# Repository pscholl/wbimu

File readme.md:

A re-configurable standalone board including the latest Bosch inertial sensors. Includes a gyroscope, accelerometer, magnetometer, humidity, pressure and temperature. The board is 13x22mm large.

 The board can either be used battery-powered in a standalone fashion, or connected to a Linux machine via USB Type C.
 By using the Bosch BMF a fully reprogrammable ARM M0 core is included on the board, which can control the system in standalone operation. 
 The MCP2210 USB-SPI bridge can control all components when connected to a PC.
 Wireless communication is provided by Decawave's DWM100 modules, which provides ultra-wideband communication and ranging with an accuracy of 10cms.
 Power can either be supplied via USB or by a li-ion battery, a charger is included on the board.

 The system is currently under testing, ieee802.15.4- and tcp/ip-compliant linux drivers are currently being developed.

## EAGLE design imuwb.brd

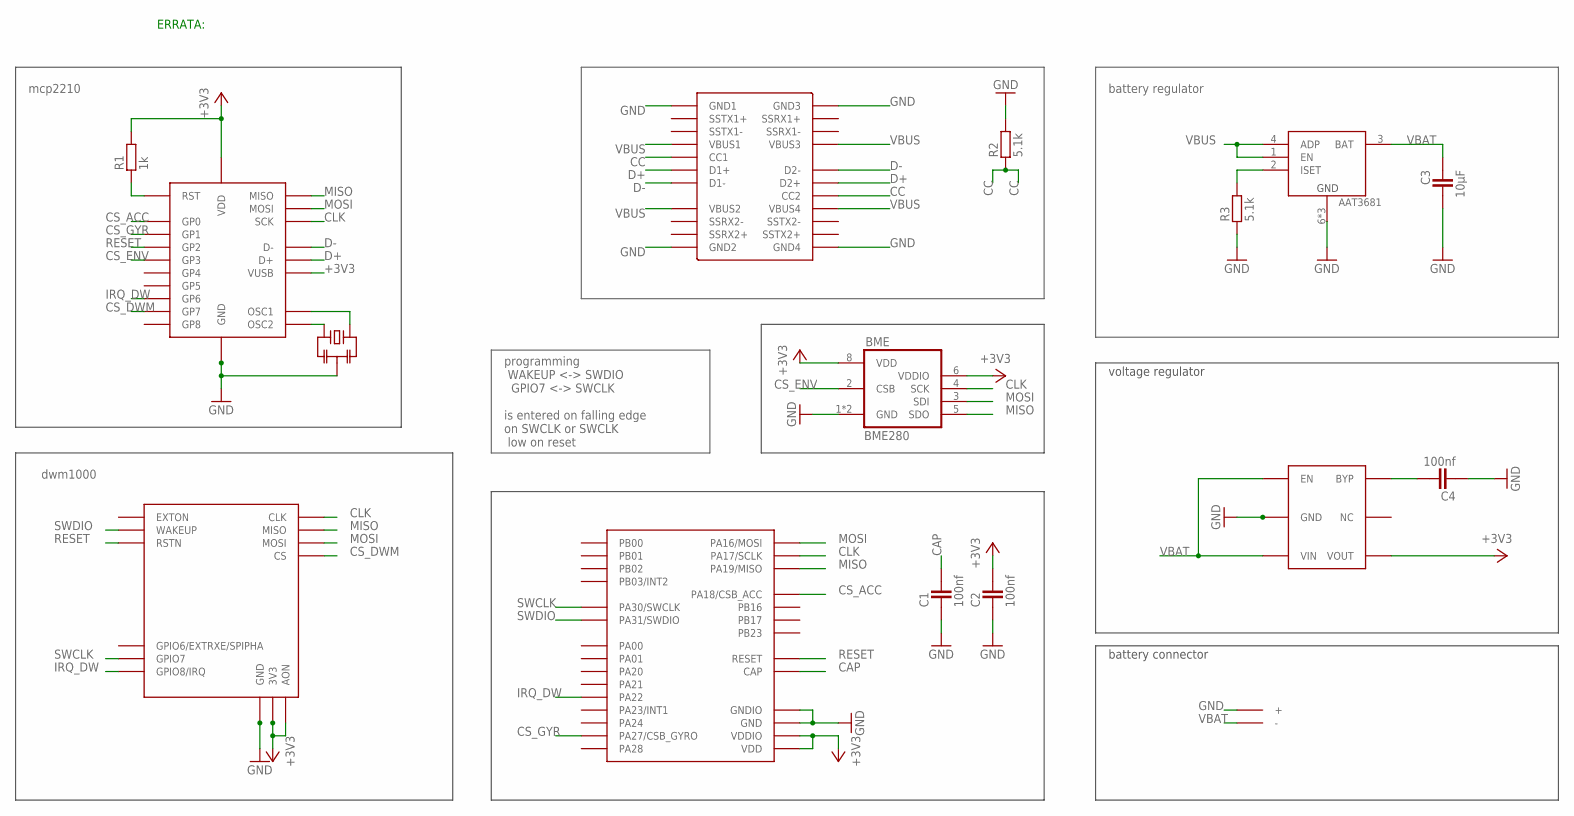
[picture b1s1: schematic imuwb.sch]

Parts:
AAT3681: AAT3681A; SC70JW-8; PARTNO AAT3681AIJS-4.2-T1
BME: BME280; PARTNO 262-BME280
BMF: BMF055; LGA-28; PARTNO 262-BMF055
C1, C2, C4: 100nf; CAPC1005X60N
C3: 10µF; CAPC1608X92N
DWM: DWM1000_SPECIAL; DWM1000_CASTELLATED_SPECIAL; PARTNO dwm1000
MCP2210: MCP2210; QFN-20; PARTNO 579-MCP2210TIMQ
OSC: CSTCE; CSCTE_G15C; PARTNO PRQC12.00CR1010V00L
R1: 1k; RESC1005X40AN
R2, R3: 5.1k; RESC1005X40AN
U$1: MIC53533.3V; MIC5353
U$2: BATPADS
USBC: USBC_NOSBU; KEYSTONE_953_NOPADS_NOSBU

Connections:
+3V3: BME.6 (VDDIO), BME.8 (VDD), BMF.P$3 (VDD), BMF.P$28 (VDDIO), C2.2, DWM.P$29 (AON), DWM.P$30 (3V3), DWM.P$31 (3V3_1), MCP2210.P$14 (VUSB), MCP2210.P$18 (VDD), R1.2, U$1.P$6 (VOUT)
CAP: BMF.P$9 (CAP), C1.2
CC: R2.1, USBC.P$5 (CC2), USBC.P$17 (CC1)
CLK: BME.4 (SCK), BMF.P$23 (PA17/SCLK), DWM.P$44 (CLK), MCP2210.P$8 (SCK)
CS_ACC: BMF.P$22 (PA18/CSB_ACC), MCP2210.P$2 (GP0)
CS_DWM: DWM.P$41 (CS), MCP2210.P$12 (GP7)
CS_ENV: BME.2 (CSB), MCP2210.P$5 (GP3)
CS_GYR: BMF.P$12 (PA27/CSB_GYRO), MCP2210.P$3 (GP1)
D+: MCP2210.P$16 (D+), USBC.P$6 (D2+), USBC.P$18 (D1+)
D-: MCP2210.P$15 (D-), USBC.P$7 (D2-), USBC.P$19 (D1-)
GND: AAT3681.6 (GND), AAT3681.7 (GND), AAT3681.8 (GND), BME.1 (GND), BME.7 (GND), BMF.P$2 (GND), BMF.P$25 (GNDIO), C1.1, C2.1, C3.2, C4.1, DWM.P$32 (GND), DWM.P$40 (GND1), DWM.P$45 (GND2), DWM.P$47 (GND3), DWM.P$48 (GND4), MCP2210.P$17 (GND), MCP2210.P$21 (GND1), OSC.P$2 (2), R2.2, R3.1, U$1.P$2 (GND), U$1.P$7 (GND1), U$2.P$1 (+), USBC.P$1 (GND4), USBC.P$12 (GND3), USBC.P$13 (GND1), USBC.P$24 (GND2)
IRQ_DW: BMF.P$16 (PA22), DWM.P$46 (GPIO8/IRQ), MCP2210.P$11 (GP6)
MISO: BME.5 (SDO), BMF.P$21 (PA19/MISO), DWM.P$43 (MISO), MCP2210.P$10 (MISO)
MOSI: BME.3 (SDI), BMF.P$24 (PA16/MOSI), DWM.P$42 (MOSI), MCP2210.P$6 (MOSI)
unnamed: MCP2210.P$20 (OSC2), OSC.P$1 (1)
unnamed: MCP2210.P$19 (OSC1), OSC.P$3 (3)
unnamed: AAT3681.2 (ISET), R3.2
unnamed: C4.2, U$1.P$4 (BYP)
unnamed: MCP2210.P$1 (RST), R1.1
RESET: BMF.P$11 (RESET), DWM.P$27 (RSTN), MCP2210.P$4 (GP2)
SWCLK: BMF.P$8 (PA30/SWCLK), DWM.P$28 (GPIO7)
SWDIO: BMF.P$7 (PA31/SWDIO), DWM.P$26 (WAKEUP)
VBAT: AAT3681.3 (BAT), C3.1, U$1.P$1 (EN), U$1.P$3 (VIN), U$2.P$2 (-)
VBUS: AAT3681.1 (EN), AAT3681.4 (ADP), USBC.P$4 (VBUS4), USBC.P$9 (VBUS3), USBC.P$16 (VBUS1), USBC.P$21 (VBUS2)

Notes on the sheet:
mcp2210
dwm1000
programming WAKEUP <-> SWDIO GPIO7 <-> SWCLK is entered on falling edge on SWCLK or SWCLK low on reset
battery regulator
ERRATA:
voltage regulator
battery connector

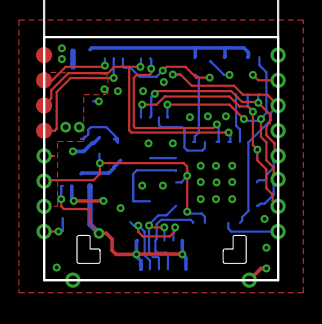
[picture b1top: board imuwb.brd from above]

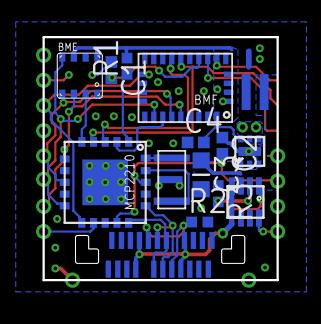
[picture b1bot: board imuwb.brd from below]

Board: 2 copper layers, 13.0 x 13.5 mm, 16 parts (15 on the bottom side), 24 nets.

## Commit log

2016-06-14 new version
2016-06-14 updates to the BOM

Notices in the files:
parts and their libraries:
SparkFun-Aesthetics: Licensing: Creative Commons ShareAlike 4.0 International - https://creativecommons.org/licenses/by-sa/4.0
